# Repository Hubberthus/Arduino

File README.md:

Arduino core for ESPExtra module based on the "Arduino core for ESP8266 WiFi chip" project
==========================================================================================

This fork contains an additional module called ESPExtra, which is an ESP8266-based module using MCP23S17 and MCP3008 ICs to allow the usage of additional 32 digital GPIO and 8 analog input pins.
It can be accessed in the "espextra" branch.

The ESPExtra appears as a new variant which you can choose in Arduino IDE.
It contains several modifications in the ESP8266 core code, mostly for digital and analog GPIO access. The additional pins can be set/read/written using the standard Arduino functions.

Generally it can be used simply as an Arduino board, just look out for the pin numbering because most of the ESP8266's pins are for internal usage only. Please use the A0...A8, D0...D31 and CS_0...CS_2 constants for accessing the GPIOs.

For more information about the usage of the ESPExtra, please look at the Wiki page:
(https://github.com/Hubberthus/ESPExtra/wiki)

Below is the original "README.md" file:
(TODO: Update installation information)

Arduino core for ESP8266 WiFi chip
===========================================

This project brings support for ESP8266 chip to the Arduino environment. It lets you write sketches using familiar Arduino functions and libraries, and run them directly on ESP8266, no external microcontroller required.

ESP8266 Arduino core comes with libraries to communicate over WiFi using TCP and UDP, set up HTTP, mDNS, SSDP, and DNS servers, do OTA updates, use a file system in flash memory, work with SD cards, servos, SPI and I2C peripherals.

# Contents
- Installing options:
  - [Using Boards Manager](#installing-with-boards-manager)
  - [Using git version](#using-git-version)
  - [Using PlatformIO](#using-platformio)
  - [Building with make](#building-with-make)
- [Documentation](#documentation)
- [Issues and support](#issues-and-support)
- [Contributing](#contributing)  
- [License and credits](#license-and-credits)   

### Installing with Boards Manager ###

Starting with 1.6.4, Arduino allows installation of third-party platform packages using Boards Manager. We have packages available for Windows, Mac OS, and Linux (32 and 64 bit).

- Install Arduino 1.6.8 from the [Arduino website](http://www.arduino.cc/en/main/software).
- Start Arduino and open Preferences window.
- Enter ```http://arduino.esp8266.com/stable/package_esp8266com_index.json``` into *Additional Board Manager URLs* field. You can add multiple URLs, separating them with commas.
- Open Boards Manager from Tools > Board menu and install *esp8266* platform (and don't forget to select your ESP8266 board from Tools > Board menu after installation).

The best place to ask questions related to this core is ESP8266 community forum: http://www.esp8266.com/arduino.
If you find this forum or the ESP8266 Boards Manager package useful, please consider supporting it with a donation. <br />

#### Available versions

##### Stable version 
Boards manager link: `http://arduino.esp8266.com/stable/package_esp8266com_index.json`

Documentation: [http://esp8266.github.io/Arduino/versions/2.3.0/](http://esp8266.github.io/Arduino/versions/2.3.0/)

##### Staging version 
Boards manager link: `http://arduino.esp8266.com/staging/package_esp8266com_index.json`

Documentation: [http://esp8266.github.io/Arduino/versions/2.3.0-rc2/](http://esp8266.github.io/Arduino/versions/2.3.0-rc2/)

### Using git version

- Install Arduino 1.6.8
- Go to Arduino directory
- Clone this repository into hardware/esp8266com/esp8266 directory (or clone it elsewhere and create a symlink)
```bash
cd hardware
mkdir esp8266com
cd esp8266com
git clone https://github.com/esp8266/Arduino.git esp8266
```
- Download binary tools (you need Python 2.7)
```bash
cd esp8266/tools
python get.py
```
- Restart Arduino

### Using PlatformIO

[PlatformIO](http://platformio.org) is an open source ecosystem for IoT
development with cross platform build system, library manager and full support
for Espressif (ESP8266) development. It works on the popular host OS: Mac OS X, Windows,
Linux 32/64, Linux ARM (like Raspberry Pi, BeagleBone, CubieBoard).

- [What is PlatformIO?](http://docs.platformio.org/en/stable/what-is-platformio.html)
- [PlatformIO IDE](http://platformio.org/platformio-ide)
- Quick Start with [PlatformIO IDE](http://docs.platformio.org/en/stable/ide/atom.html#quick-start) or [PlatformIO CLI](http://docs.platformio.org/en/stable/quickstart.html)
- [Advanced using](http://docs.platformio.org/en/stable/platforms/espressif.html) -
  custom settings, uploading to SPIFFS, Over-the-Air (OTA) or using stage version
- [Integration with other IDE](http://docs.platformio.org/en/stable/ide.html) -
  Atom, CLion, Eclipse, Emacs, NetBeans, Qt Creator, Sublime Text, VIM and Visual Studio
- [Project Examples](http://docs.platformio.org/en/stable/platforms/espressif.html#examples)

### Building with make

[makeEspArduino](https://github.com/plerup/makeEspArduino) is a generic makefile for any ESP8266 Arduino project.
Using make instead of the Arduino IDE makes it easier to do automated and production builds.

### Documentation

Documentation for latest development version:

- [Reference](doc/reference.md)
- [Libraries](doc/libraries.md)
- [File system](doc/filesystem.md)
- [OTA update](doc/ota_updates/readme.md)
- [Supported boards](doc/boards.md)
- [FAQ / Trubleshooting](doc/faq/readme.md)
- [Change log](doc/changes.md)

### Issues and support ###

If you encounter an issue, you are welcome to submit it here on Github: https://github.com/esp8266/Arduino/issues.
Please provide as much context as possible: version which you are using (you can check it in Boards Manager), your sketch code, serial output, board model, IDE settings (board selection, flash size, etc).

If you can not find the answers above, you can also try [ESP8266 Community Forum](http://www.esp8266.com/arduino)

### Contributing

For minor fixes of code and documentation, go ahead and submit a pull request.

Check out the list of issues which are easy to fix — [easy issues for 2.2.0](https://github.com/esp8266/Arduino/issues?q=is%3Aopen+is%3Aissue+milestone%3A2.2.0+label%3A%22level%3A+easy%22). Working on them is a great way to move the project forward.

Larger changes (rewriting parts of existing code from scratch, adding new functions to the core, adding new libraries) should generally be discussed [in the chat](https://gitter.im/esp8266/Arduino) first.

Feature branches with lots of small commits (especially titled "oops", "fix typo", "forgot to add file", etc.) should be squashed before opening a pull request. At the same time, please refrain from putting multiple unrelated changes into a single pull request.

### License and credits ###

Arduino IDE is developed and maintained by the Arduino team. The IDE is licensed under GPL.

ESP8266 core includes an xtensa gcc toolchain, which is also under GPL.

Esptool written by Christian Klippel is licensed under GPLv2, currently maintained by Ivan Grokhotkov: https://github.com/igrr/esptool-ck.

Espressif SDK included in this build is under Espressif MIT License.

ESP8266 core files are licensed under LGPL.

[SPI Flash File System (SPIFFS)](https://github.com/pellepl/spiffs) written by Peter Andersson is used in this project. It is distributed under MIT license.

[umm_malloc](https://github.com/rhempel/umm_malloc) memory management library written by Ralph Hempel is used in this project. It is distributed under MIT license.

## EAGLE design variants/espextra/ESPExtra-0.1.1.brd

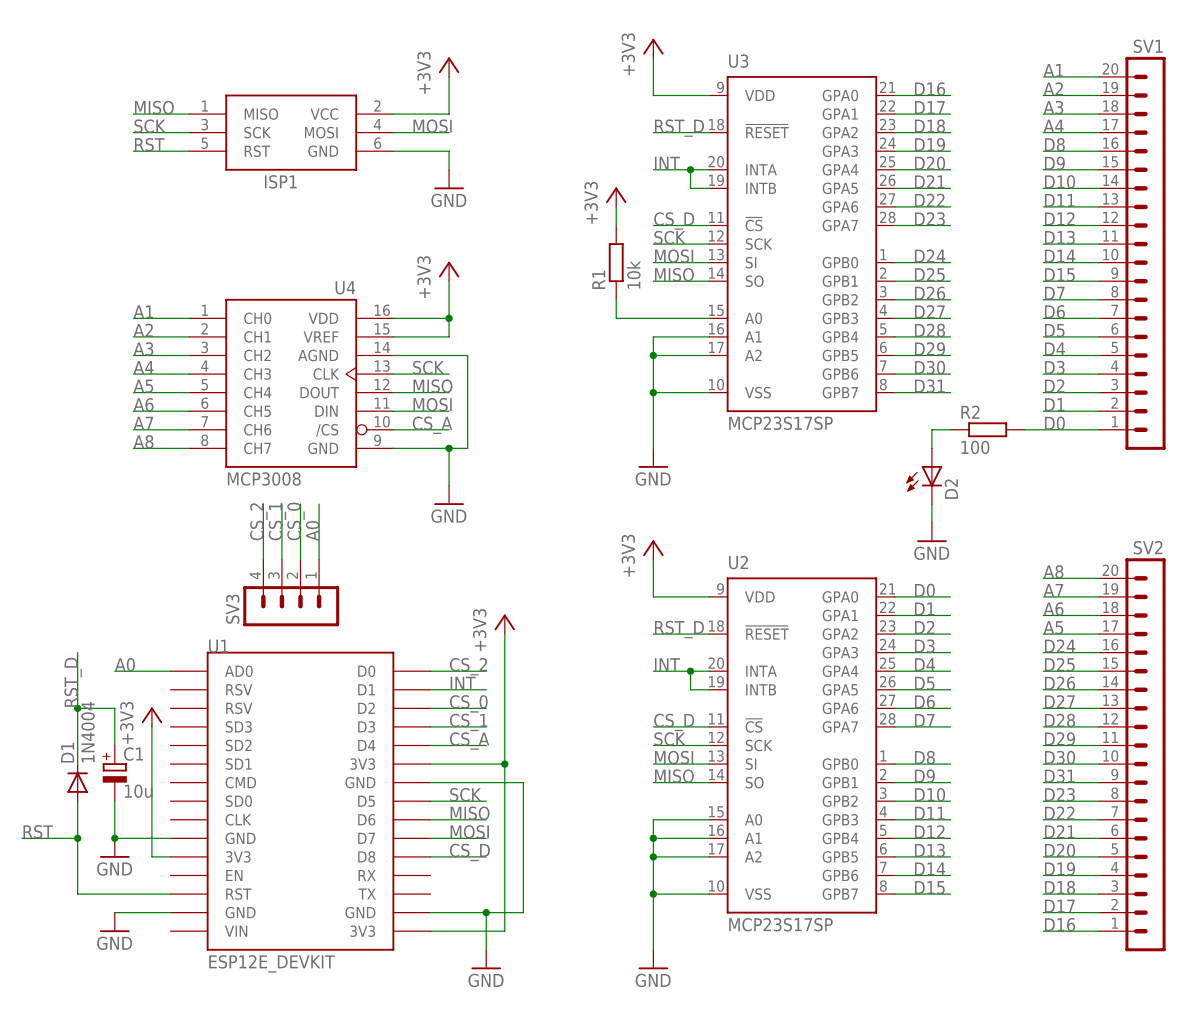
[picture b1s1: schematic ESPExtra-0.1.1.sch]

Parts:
C1: 10u; E2,5-5
D1: 1N4004; DO41-10
D2: LED3MM
ISP1: AVRISP-6; AVRISP
R1: 10k; 0204/5
R2: 100; 0204/5
SV1, SV2: MA20-1
SV3: MA04-1
U1: ESP12E_DEVKIT
U2, U3: MCP23S17SP; DIL28-3
U4: MCP3008; DIL16

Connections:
+3V3: ISP1.2 (VCC), R1.2, U1.3V3@0 (3V3), U1.3V3@1 (3V3), U1.3V3@2 (3V3), U2.9 (VDD), U3.9 (VDD), U4.15 (VREF), U4.16 (VDD)
A0: SV3.1, U1.AD0
A1: SV1.20, U4.1 (CH0)
A2: SV1.19, U4.2 (CH1)
A3: SV1.18, U4.3 (CH2)
A4: SV1.17, U4.4 (CH3)
A5: SV2.17, U4.5 (CH4)
A6: SV2.18, U4.6 (CH5)
A7: SV2.19, U4.7 (CH6)
A8: SV2.20, U4.8 (CH7)
CS_0: SV3.2, U1.D2
CS_1: SV3.3, U1.D3
CS_2: SV3.4, U1.D0
CS_A: U1.D4, U4.10 (/CS)
CS_D: U1.D8, U2.11 (!CS), U3.11 (!CS)
D0: R2.2, SV1.1, U2.21 (GPA0)
D1: SV1.2, U2.22 (GPA1)
D2: SV1.3, U2.23 (GPA2)
D3: SV1.4, U2.24 (GPA3)
D4: SV1.5, U2.25 (GPA4)
D5: SV1.6, U2.26 (GPA5)
D6: SV1.7, U2.27 (GPA6)
D7: SV1.8, U2.28 (GPA7)
D8: SV1.16, U2.1 (GPB0)
D9: SV1.15, U2.2 (GPB1)
D10: SV1.14, U2.3 (GPB2)
D11: SV1.13, U2.4 (GPB3)
D12: SV1.12, U2.5 (GPB4)
D13: SV1.11, U2.6 (GPB5)
D14: SV1.10, U2.7 (GPB6)
D15: SV1.9, U2.8 (GPB7)
D16: SV2.1, U3.21 (GPA0)
D17: SV2.2, U3.22 (GPA1)
D18: SV2.3, U3.23 (GPA2)
D19: SV2.4, U3.24 (GPA3)
D20: SV2.5, U3.25 (GPA4)
D21: SV2.6, U3.26 (GPA5)
D22: SV2.7, U3.27 (GPA6)
D23: SV2.8, U3.28 (GPA7)
D24: SV2.16, U3.1 (GPB0)
D25: SV2.15, U3.2 (GPB1)
D26: SV2.14, U3.3 (GPB2)
D27: SV2.13, U3.4 (GPB3)
D28: SV2.12, U3.5 (GPB4)
D29: SV2.11, U3.6 (GPB5)
D30: SV2.10, U3.7 (GPB6)
D31: SV2.9, U3.8 (GPB7)
GND: C1.-, D2.K (C), ISP1.6 (GND), U1.GND@0 (GND), U1.GND@1 (GND), U1.GND@2 (GND), U1.GND@3 (GND), U2.10 (VSS), U2.15 (A0), U2.16 (A1), U2.17 (A2), U3.10 (VSS), U3.16 (A1), U3.17 (A2), U4.9 (GND), U4.14 (AGND)
INT: U1.D1, U2.19 (INTB), U2.20 (INTA), U3.19 (INTB), U3.20 (INTA)
MISO: ISP1.1 (MISO), U1.D6, U2.14 (SO), U3.14 (SO), U4.12 (DOUT)
MOSI: ISP1.4 (MOSI), U1.D7, U2.13 (SI), U3.13 (SI), U4.11 (DIN)
unnamed: D2.A, R2.1
unnamed: R1.1, U3.15 (A0)
RST: D1.A, ISP1.5 (RST), U1.RST
RST_D: C1.+, D1.C, U2.18 (!RESET), U3.18 (!RESET)
SCK: ISP1.3 (SCK), U1.D5, U2.12 (SCK), U3.12 (SCK), U4.13 (CLK)

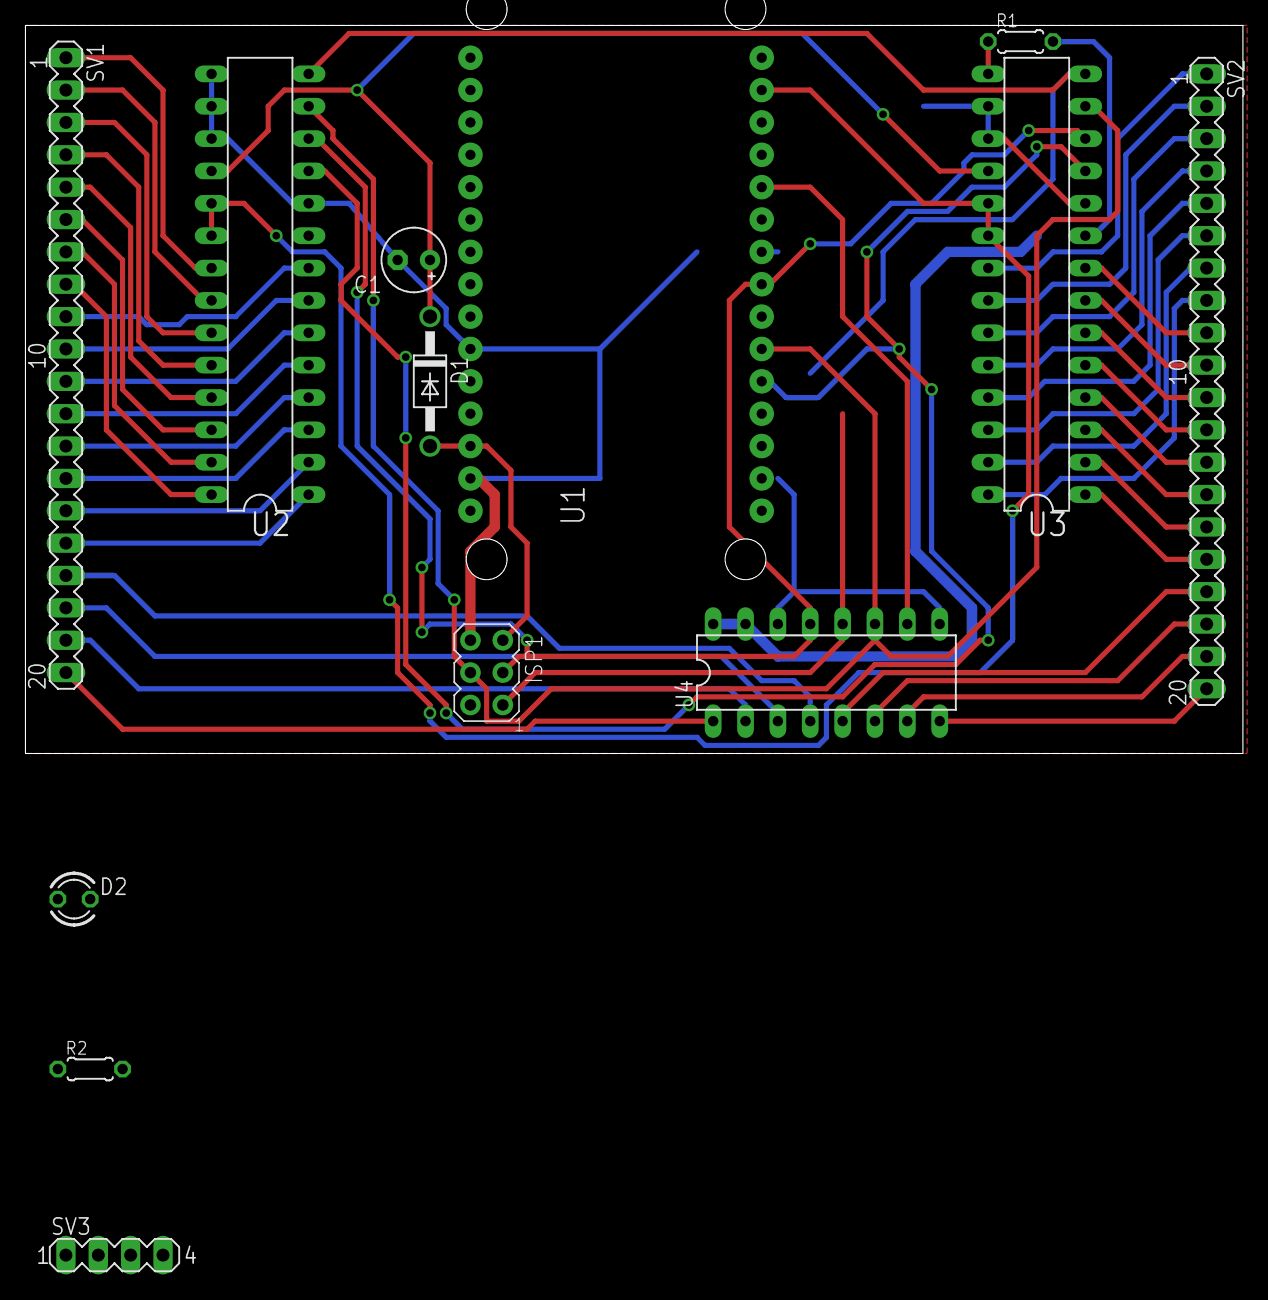
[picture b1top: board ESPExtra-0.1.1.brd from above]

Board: 2 copper layers, 95.6 x 57.1 mm, 13 parts (0 on the bottom side), 56 nets.

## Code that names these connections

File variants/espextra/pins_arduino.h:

/*
  pins_arduino.h - Pin definition functions for Arduino
  Part of Arduino - http://www.arduino.cc/

  Copyright (c) 2007 David A. Mellis
  Modified for ESPExtra variant by Norbert Fekete, 2016.

  This library is free software; you can redistribute it and/or
  modify it under the terms of the GNU Lesser General Public
  License as published by the Free Software Foundation; either
  version 2.1 of the License, or (at your option) any later version.

  This library is distributed in the hope that it will be useful,
  but WITHOUT ANY WARRANTY; without even the implied warranty of
  MERCHANTABILITY or FITNESS FOR A PARTICULAR PURPOSE.  See the GNU
  Lesser General Public License for more details.

  You should have received a copy of the GNU Lesser General
  Public License along with this library; if not, write to the
  Free Software Foundation, Inc., 59 Temple Place, Suite 330,
  Boston, MA  02111-1307  USA

  $Id: wiring.h 249 2007-02-03 16:52:51Z mellis $
*/

#ifndef Pins_Arduino_h
#define Pins_Arduino_h

#include "../generic/common.h"

#ifdef __cplusplus
extern "C" {
#endif

#define NUM_EXTERNAL_DIGITAL_PINS  32
#define NUM_INTERNAL_DIGITAL_PINS  17
#define NUM_DIGITAL_PINS           (NUM_INTERNAL_DIGITAL_PINS + NUM_EXTERNAL_DIGITAL_PINS)
#define NUM_EXTERNAL_ANALOG_INPUTS 8
#define NUM_INTERNAL_ANALOG_INPUTS 1
#define NUM_ANALOG_INPUTS          (NUM_INTERNAL_ANALOG_INPUTS + NUM_EXTERNAL_ANALOG_INPUTS)
#define NUM_INTERNAL_PINS          (NUM_INTERNAL_DIGITAL_PINS + NUM_INTERNAL_ANALOG_INPUTS)

#define digitalPinHasPWM(p)        (((p) >= NUM_INTERNAL_PINS && (p) < NUM_DIGITAL_PINS + NUM_INTERNAL_ANALOG_INPUTS)? 1 : 0)
#define digitalPinToInterrupt(p)   (((p) < EXTERNAL_NUM_INTERRUPTS) || digitalPinHasPWM(p)? (p) : NOT_AN_INTERRUPT)

#define digitalPinToPort(pin)       (((pin) < NUM_INTERNAL_PINS ? 0 : \
		((pin) < NUM_DIGITAL_PINS + NUM_INTERNAL_ANALOG_INPUTS ? PORT_LIST[0] : 0)))
#define digitalPinToBitMask(pin)    ((pin) < NUM_INTERNAL_PINS ? 1UL << (pin) : 1 << (pin - NUM_INTERNAL_PINS))
#define digitalPinToTimer(pin)      ((pin) < NUM_INTERNAL_PINS ? 0 : -1)
#define portOutputRegister(port)    ((pin) < NUM_INTERNAL_PINS ? (volatile uint32_t*) &GPO : PORT_LIST[0])
#define portInputRegister(port)     ((pin) < NUM_INTERNAL_PINS ? (volatile uint32_t*) &GPI : PORT_LIST[0])
#define portModeRegister(port)      ((pin) < NUM_INTERNAL_PINS ? (volatile uint32_t*) &GPE : PORT_LIST[0])

// ESP8266 pins

#define CS_MCP23S17  15  // D8: TX1/HCS (pull down on boot)
#define CS_MCP3008    2  // D4: bootstrap TX/blue LED (pull up on boot)
#define CS_0          4  // D2
#define CS_1          0  // D3: flash (pull up on boot)
#define CS_2         16  // D0: user/wake/red LED

#define INT_GPIO      5  // D1

#define SDA           4  // CS_0 / D2
#define SCL           0  // CS_1 / D3

// Expanded pins

#define LED_BUILTIN  (NUM_INTERNAL_PINS)
#define BUILTIN_LED  (NUM_INTERNAL_PINS)

// PORTA
#define D0  (NUM_INTERNAL_PINS)
#define D1  (NUM_INTERNAL_PINS + 1)
#define D2  (NUM_INTERNAL_PINS + 2)
#define D3  (NUM_INTERNAL_PINS + 3)
#define D4  (NUM_INTERNAL_PINS + 4)
#define D5  (NUM_INTERNAL_PINS + 5)
#define D6  (NUM_INTERNAL_PINS + 6)
#define D7  (NUM_INTERNAL_PINS + 7)
// PORTB
#define D8   (NUM_INTERNAL_PINS + 8)
#define D9   (NUM_INTERNAL_PINS + 9)
#define D10  (NUM_INTERNAL_PINS + 10)
#define D11  (NUM_INTERNAL_PINS + 11)
#define D12  (NUM_INTERNAL_PINS + 12)
#define D13  (NUM_INTERNAL_PINS + 13)
#define D14  (NUM_INTERNAL_PINS + 14)
#define D15  (NUM_INTERNAL_PINS + 15)
// PORTC
#define D16  (NUM_INTERNAL_PINS + 16)
#define D17  (NUM_INTERNAL_PINS + 17)
#define D18  (NUM_INTERNAL_PINS + 18)
#define D19  (NUM_INTERNAL_PINS + 19)
#define D20  (NUM_INTERNAL_PINS + 20)
#define D21  (NUM_INTERNAL_PINS + 21)
#define D22  (NUM_INTERNAL_PINS + 22)
#define D23  (NUM_INTERNAL_PINS + 23)
// PORTD
#define D24  (NUM_INTERNAL_PINS + 24)
#define D25  (NUM_INTERNAL_PINS + 25)
#define D26  (NUM_INTERNAL_PINS + 26)
#define D27  (NUM_INTERNAL_PINS + 27)
#define D28  (NUM_INTERNAL_PINS + 28)
#define D29  (NUM_INTERNAL_PINS + 29)
#define D30  (NUM_INTERNAL_PINS + 30)
#define D31  (NUM_INTERNAL_PINS + 31)

#define A1  (NUM_DIGITAL_PINS + NUM_INTERNAL_ANALOG_INPUTS)
#define A2  (NUM_DIGITAL_PINS + NUM_INTERNAL_ANALOG_INPUTS + 1)
#define A3  (NUM_DIGITAL_PINS + NUM_INTERNAL_ANALOG_INPUTS + 2)
#define A4  (NUM_DIGITAL_PINS + NUM_INTERNAL_ANALOG_INPUTS + 3)
#define A5  (NUM_DIGITAL_PINS + NUM_INTERNAL_ANALOG_INPUTS + 4)
#define A6  (NUM_DIGITAL_PINS + NUM_INTERNAL_ANALOG_INPUTS + 5)
#define A7  (NUM_DIGITAL_PINS + NUM_INTERNAL_ANALOG_INPUTS + 6)
#define A8  (NUM_DIGITAL_PINS + NUM_INTERNAL_ANALOG_INPUTS + 7)

#ifdef __cplusplus
} // extern "C"
#endif

#endif /* Pins_Arduino_h */

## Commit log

2016-10-21 Initial ESPExtra commit. 32 GPIOs using two MCP23S17 ICs
2016-10-21 Fixing board identification macros
2016-10-21 MCP23S17 code refactoring, using less IRAM
2016-10-24 Added support for MCP3008 analog input
2016-10-24 Added EEPROM native access. For now only usable in one cpp file.
2016-10-25 Board schematics and layout for v0.1
2016-10-26 Removed unnecessary duplicates from board
2016-10-26 Previous commit failed to update board files
2016-10-26 After second thought, wrapping the whole 'avr' directory is not relevant. User application should use appropriate alternatives for EEPROM, progmem, interrupts, etc.
2016-10-26 Resistor removed, internal pullup is used for interrupt pin. Also, before SPI transactions, set the appropriate SPI settings, just to be sure.
2016-11-02 Ignore Eclipse project files and settings directory
2016-11-02 Updated the board schematic to use 3V3. Using 5V is not working.
2016-11-04 SPI speedup. Also stripboard image added
2016-11-11 Initial PWM test for ESPExtra. D0-D15 can be used as PWM pins. NMI is not good for the interrupt because of the SPI
2016-11-14 PWM got #define-s, and I2C default pins added
2016-11-15 Some SPI speed optimization and interrupt handling fix
2016-11-15 GPIO interrupt handling added
2016-11-16 GPIO interrupt handling corrections
2016-11-16 SPI library includes interrupt handling for transactions. Also HW CS pin usage and SPI ending is disabled for ESPExtra.
2016-11-17 Some useful definitions, and a handy include
2016-11-24 pinMode bugfix + digitalWrite on an input pin sets pullup accordingly
2016-11-24 Changed pin consts to #defines so they can be used in macros
2016-11-24 Fixed bug: only first 8 digital outputs were working
2016-11-25 Interrupt bugfix + flushing of all outputs added
